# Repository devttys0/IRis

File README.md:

What?
=====

IRis is a low power, low cost, high sensitivity infrared detector designed for capturing raw IR digital data transmissions. Think of it like a mon0 interface for IR.

Why?
====

Typical [IR](https://www.sparkfun.com/products/10266) [receivers](http://dangerousprototypes.com/docs/USB_IR_Toy_v2) are designed to work with common IR remote controls, and as such they ignore any IR signals that are not [modulated at 36-38kHz](http://www.vishay.com/docs/80071/dataform.pdf). But there is so much more to the world of IR than this!

In contrast, IRis was designed to be a simple, general purpose IR detector to aid in the capture and analysis of raw IR transmissions, in particular low data rate signals such as those emitted by chell phone proximity sensors.

Who?
====

The brainchild of [Dale Wooden](https://www.linkedin.com/in/dale-wooden-1b1bb288), and designed by [Craig Heffner](http://www.analogzoo.com), IRis is of use to anyone interested in exploring the hidden world of IR around them!

How?
====

Most IR data is transmitted via on/off pulses (i.e., on-off keying). Powered from a single CR2032 coin cell battery, IRis uses a a sensitive photodiode, high gain transimpedance amplifier, and comparator to detect even very weak IR signals and convert them back into clean digital pulses that can be interpreted and analyzed by nearly any digital system, such as an Arduino or Raspberry Pi. Just connect to the IRis' output pins (connector P1) and point it at an IR source!

Due to its high sensitivity, best performance is obtained by preventing unwanted or ambient light from hitting the IRis photodiode. In conditions where there is low ambient light this is not a major problem, and in areas of greater illumination the issue can be mitigated by placing a shroud around the IR detector to prevent direct contact with unwated light. IR filters can also be used to reduce interference from unwanted light sources, but bear in mind that some bright light sources (e.g., the sun!) emit IR radiation as well.

IRis is still able to detect IR transmissions in the presence of bright ambient light, but at a reduced distance.

How Much?
=========

PCBs (1.24 inches in diameter) are available from [OSHPark](https://oshpark.com/shared_projects/OFeMS3Ed) for less than $8, and components can be ordered in single quantities from [Digikey](./digikey_bom.csv) for an additional $8.

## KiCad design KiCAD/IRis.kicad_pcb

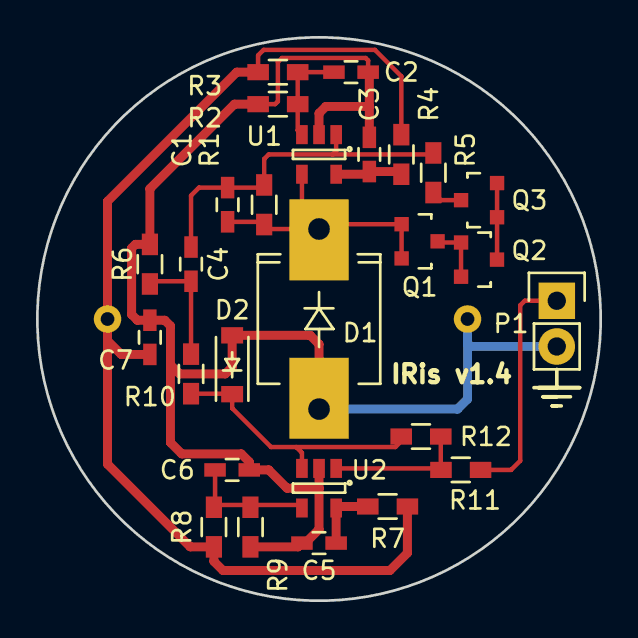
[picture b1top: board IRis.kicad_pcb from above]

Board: 2 copper layers, 31.3 x 31.3 mm, 28 parts (1 on the bottom side), 15 nets.

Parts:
BT1: 3v; MPD BH32T-C
C1: 2.2pF; C_0603_HandSoldering
C2, C3, C4, C5, C6: 0.1uF; C_0603_HandSoldering
C7: 10uF; C_0603_HandSoldering
D1: VBPW34FASR; SMC-RM10_Universal_Handsoldering
D2: MBR0520; SOD-123
P1: Digital Out; Pin_Header_Straight_1x02
Q1, Q2, Q3: MMBF4117; SOT-23
R1: 10M; R_0603_HandSoldering
R2: 22k; R_0603_HandSoldering
R3: 330k; R_0603_HandSoldering
R4, R7: 10; R_0603_HandSoldering
R5: 0; R_0603_HandSoldering
R6, R10: 5.1k; R_0603_HandSoldering
R8, R12: 680k; R_0603_HandSoldering
R9: 10k; R_0603_HandSoldering
R11: 100; R_0603_HandSoldering
U1: TSV911ILT; SOT-23-5
U2: TLV3201; SOT-23-5

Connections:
+5V: BT1.1, C7.1, R3.2, R4.2, R7.2, R8.1
GND: BT1.2, C2.2, C3.1, C5.1, C6.2, C7.2, D1.2, D2.2, P1.2, R2.1, R6.1, R9.1, U1.2, U2.2
unnamed: C1.1, C4.2, R1.1, R5.2, U1.1
unnamed: C1.2, D1.1, Q1.1, Q1.2, R1.2, U1.4
unnamed: C2.1, R2.2, R3.1, U1.3
unnamed: C3.2, R4.1, U1.5
unnamed: C4.1, R6.2, R10.1
unnamed: C5.2, R7.1, U2.5
unnamed: C6.1, R8.2, R9.2, U2.4
unnamed: D2.1, R10.2, R12.2, U2.3
unnamed: P1.1, R11.2
unnamed: Q1.3, Q2.1, Q2.2
unnamed: Q2.3, Q3.1, Q3.2
unnamed: Q3.3, R5.1
unnamed: R11.1, R12.1, U2.1

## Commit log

2016-04-15 Initial check-in
2016-05-21 Added README
2016-05-21 Directory restructure.
2016-05-21 Added schematic PDF
2016-05-21 Fixed typo
2016-05-21 Added negative voltage input protection to comparator U2; fixed copper fill clearances for OSHPark
2016-05-22 Updated board and Gerbers to v1.4
2016-06-06 Added external hysteresis to comparator
2016-06-30 Updated to latest version
2016-06-30 Updated 3D image
2016-08-08 Added ground icon to P1 silkscreen; rotated P1 180 degrees.
2016-08-09 Changed R5 to zero-ohm jumper
2016-08-09 Added ground symbol to back silk screen of jumper P1.
2016-08-09 Added test points TP1 and TP2 for monitoring the signal before and after DC blocking capacitor C4.
2016-09-17 Removed all vias from volterra PCB design
2016-09-17 Added volterra Gerbers
